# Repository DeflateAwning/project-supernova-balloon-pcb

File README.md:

# Project Supernova
A Helium Balloon, to assess the Helium Network.

## Features
This project is a PCB which is capable of being the primary payload on a PCB aboard a stratospheric helium balloon. The PCB intends to downlink 

* Onboard GPS for position tracking
* Atmospheric condition sensors (temperature/pressure/humidity) to generate downlink data
* Onboard PID-controlled heater and battery management
* Very low cost (<$100)

## Notes
* 3v3 regulated voltage. 9v unregulated battery voltage.
 
## Rev 2 Errata
1. Nothing yet (fingers crossed)

## Rev 1 Errata
1. DHT22 doesn't support 3V3 supply, technically
2. ADC2 doesn't work when wifi is enabled
3. DHT22 cannot be connected to pin D12, as D12 must be floating at boot
4. D34-D39 are input-only (so `TEMP_V+` is a problem)
5. LM335 onboard temperature sensor is basically incompatible with 3V3 systems
6. DHT22 needs a 10k pull-up to 3V3
7. RTF switch needs resistors on each leg to prevent shorting in case of a make-before-break switch.
8. The voltage regulator footprint could use the pads moved a bit (and could include through-hole pins).
9. Should've added a pull-down resistor to the heater MOSFET to prevent heating during boot.
10. Shouldn't have put a via in the pad on the MOSFET, as it prevented the gate from soldering right, then burned the MOSFET when it entered the linear region. Should've used way larger pads on the hand-soldered SOT-23 MOSFET.

### Changes made to correct errata items (Rev 1.1)
* DHT22 (`DHT_DATA`) now connected to D23 (per Errata #3).
* DHT22 now has a 10k pull-up to 3V3 (Errata #6).
* `TEMP_V+` now connected to D25 (per Errata #4), and still left connected to D35.
* LM335 onboard temperature sensor is unused.

### OFIs
* Add LED on HEATER_EN net
* Add LED polarity on silk screen
* Consider 10u cap from GND to EN for programming
* D2 is the onboard LED, so probably best to not use it
* Should have referenced this doc: https://randomnerdtutorials.com/esp32-pinout-reference-gpios/
* Add jumper to disconnect power from GPS (because it uses so much power)

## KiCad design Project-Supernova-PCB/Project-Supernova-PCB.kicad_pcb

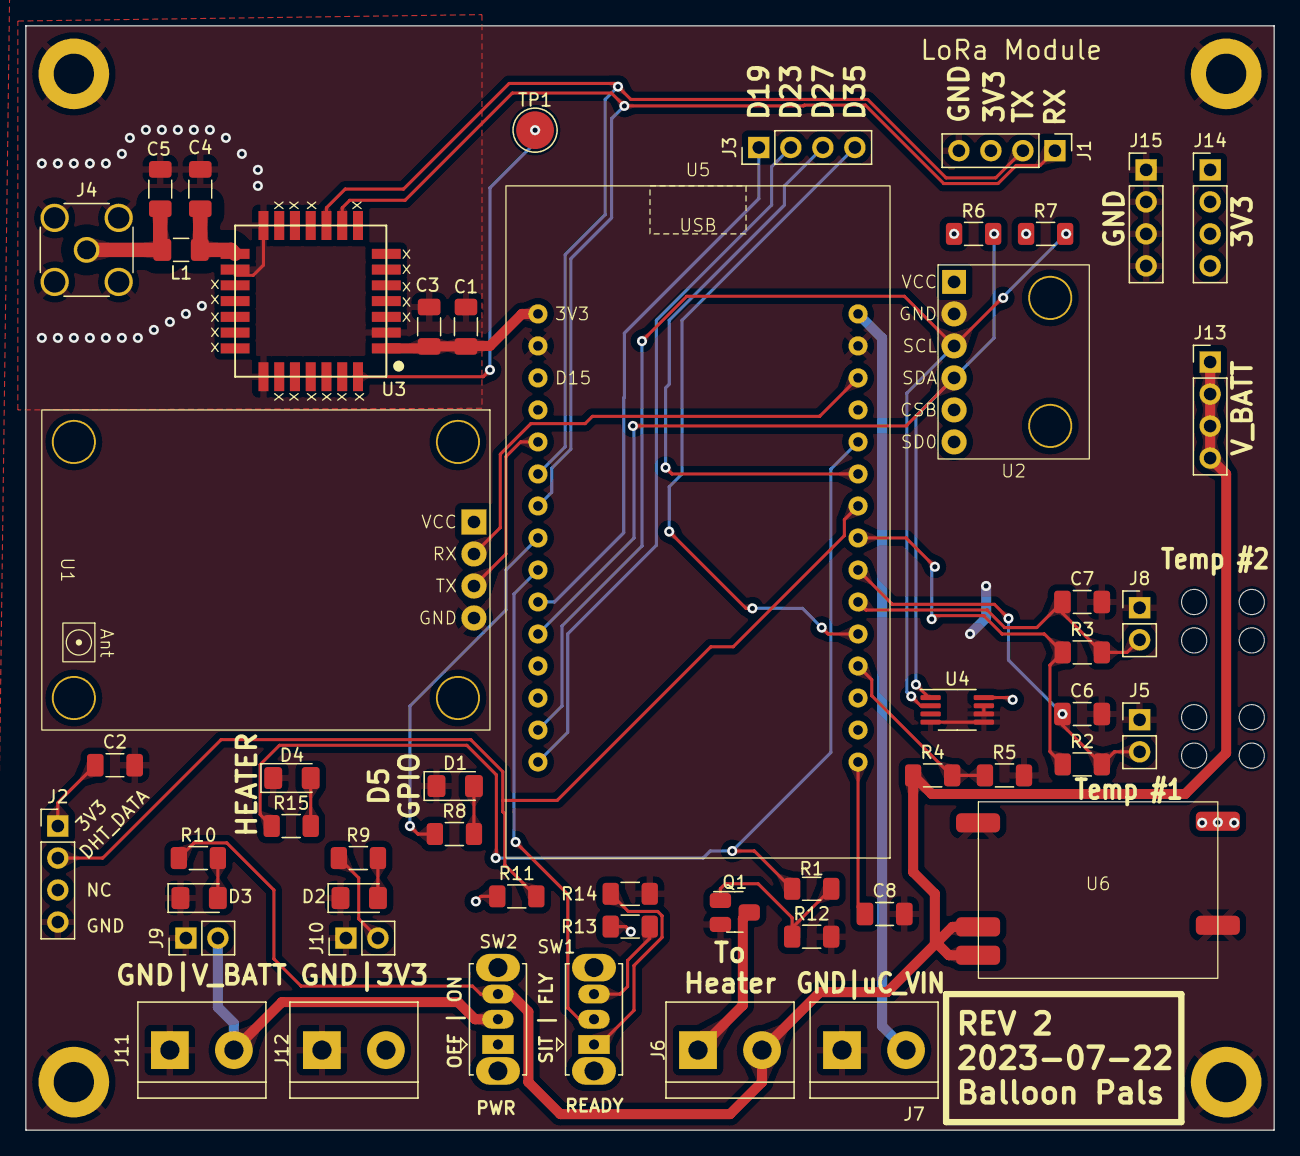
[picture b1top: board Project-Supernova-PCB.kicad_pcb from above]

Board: 2 copper layers, 99.1 x 87.6 mm, 65 parts (0 on the bottom side), 35 nets.

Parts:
C1: 100u; C_1206_3216Metric_Pad1.33x1.80mm_HandSolder
C2: 100n; C_1206_3216Metric_Pad1.33x1.80mm_HandSolder
C3: 4.7u; C_1206_3216Metric_Pad1.33x1.80mm_HandSolder
C4, C5: NC; C_1206_3216Metric_Pad1.33x1.80mm_HandSolder
C6, C7, C8: 10u; C_1206_3216Metric_Pad1.33x1.80mm_HandSolder
D1, D2, D3, D4: LED; LED_1206_3216Metric_Pad1.42x1.75mm_HandSolder
H1, H2, H3, H4: MountingHole_Pad; MountingHole_3.2mm_M3_DIN965_Pad
H5, H6, H7, H8, H9, H10, H11, H12: MountingHole; MountingHole_2mm
J1, J2, J3, J13, J14, J15: Conn_01x04; PinHeader_1x04_P2.54mm_Vertical
J4: Conn_Coaxial; SMA_Wurth_60312002114503_Vertical
J5, J8: 100k_Thermistor; PinHeader_1x02_P2.54mm_Vertical
J6, J7, J11, J12: Screw_Terminal_01x02; TerminalBlock_bornier-2_P5.08mm
J9, J10: Conn_01x02; PinHeader_1x02_P2.54mm_Vertical
L1: 0; L_1206_3216Metric_Pad1.42x1.75mm_HandSolder
Q1: AO3420; SOT-23-MassivePads-HandSolder
R1: 0; R_1206_3216Metric_Pad1.30x1.75mm_HandSolder
R2, R3: 75k; R_1206_3216Metric_Pad1.30x1.75mm_HandSolder
R4: 18k; R_1206_3216Metric_Pad1.30x1.75mm_HandSolder
R5, R6, R7, R13, R14: 4.7k; R_1206_3216Metric_Pad1.30x1.75mm_HandSolder
R8, R9, R15: 1k; R_1206_3216Metric_Pad1.30x1.75mm_HandSolder
R10, R12: 3.3k; R_1206_3216Metric_Pad1.30x1.75mm_HandSolder
R11: 10k; R_1206_3216Metric_Pad1.30x1.75mm_HandSolder
SW1, SW2: SW_SPDT; SW_Slide_1P2T_CK_OS102011MS2Q
TP1: TestPoint; TestPoint_Pad_D3.0mm
U1: GY-NEO6MV2-Module
U2: BMP280-Module
U3: LoRa-E5; LoRa-E5_HandSolder
U4: STDS75DS2F; MSOP-8_3x3mm_P0.65mm
U5: ESP32-Module-30Pin
U6: S09

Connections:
+3V3: C1.1, C2.1, C3.1, J1.3, J2.1, J10.2, J12.2, J14.1, J14.2, J14.3, J14.4, R6.1, R7.1, R9.1, R11.1, R13.1, U1.1 (VCC), U2.1 (VCC), U3.1 (VCC), U4.8 (VDD), U5.1 (3V3), U6.4 (VOUT+)
+BATT: J6.2, J13.1, J13.2, J13.3, J13.4, R4.1, R10.1, SW2.3 (C), U6.2 (VIN+), U6.3 (EN)
BATT_SENSE: R4.2, R5.1, U5.19 (D34/ADC1_CH6)
DHT_DATA: J2.2, R11.2, U5.24 (D26/ADC2_CH9/DAC2)
GND: C1.2, C2.2, C3.2, C4.2, C5.2, C6.2, C7.2, C8.2, D1.1 (K), D2.1 (K), D3.1 (K), D4.1 (K), H1.1, H2.1, H3.1, H4.1, J1.4, J2.4, J4.2 (Ext), J5.1, J7.1, J8.1, J9.1, J10.1, J11.1, J12.1, J15.1, J15.2, J15.3, J15.4, Q1.2 (S), R5.2, R12.2, R14.2, U1.4 (GND), U2.2 (GND), U3.2 (GND), U3.14 (GND), U3.16 (GND), U3.22 (GND), U4.4 (GND), U4.5 (A2), U4.6 (A1), U4.7 (A0), U5.2 (GND_2), U5.29 (GND_1), U6.1 (VIN-), U6.5 (VOUT-)
GPS_UART_MISO: U1.3 (TX), U5.5 (D4/ADC2_CH0/TOUCH0)
GPS_UART_MOSI: U1.2 (RX), U5.28 (D13/ADC2_CH4/TOUCH4/HSPI_MOSI)
HEATER_EN: R1.1, R15.1, U5.26 (D14/ADC2_CH6/TOUCH6/HSPI_CLK)
LORA_UART_MISO: J1.2, U3.10 (PB6), U5.6 (RX2/D16)
LORA_UART_MOSI: J1.1, U3.9 (PB7), U5.7 (TX2/D17)
MCU_VIN: J7.2, U5.30 (VIN)
unnamed: D1.2 (A), R8.2
unnamed: D2.2 (A), R9.2
unnamed: D3.2 (A), R10.2
unnamed: D4.2 (A), R15.2
unnamed: J3.1, U5.10 (D19/VSPI_MISO)
unnamed: J3.2, U5.15 (D23/VSPI_MOSI)
unnamed: J3.3, U5.25 (D27/ADC2_CH7/TOUCH7)
unnamed: J3.4, U5.20 (D35/ADC1_CH7)
unnamed: C5.1, J4.1 (In), L1.2
unnamed: J6.1, Q1.3 (D)
unnamed: J9.2, J11.2, SW2.2 (B)
unnamed: Q1.1 (G), R1.2, R12.1
unnamed: R14.1, SW1.1 (A)
unnamed: R13.2, SW1.3 (C)
unnamed: TP1.1, U3.28 (PB0)
unnamed: C4.1, L1.1, U3.15 (RFIO)
unnamed: R8.1, U5.8 (D5/VSPI_CS0)
unnamed: C8.1, U5.16 (EN)
RTF_SWITCH: SW1.2 (B), U5.9 (D18/VSPI_CLK)
SCL: R7.2, U2.3 (SCL), U4.2 (SCL), U5.14 (D22/I2C_SCL)
SDA: R6.2, U2.4 (SDA), U4.1 (SDA), U5.11 (D21/I2C_SDA)
TEMP_SENSE_1: C6.1, J5.2, R2.2, U5.22 (D33/ADC1_CH5/TOUCH8)
TEMP_SENSE_2: C7.1, J8.2, R3.2, U5.21 (D32/ADC1_CH4/TOUCH9)
TEMP_V+: R2.1, R3.1, U5.23 (D25/ADC2_CH8/DAC1)

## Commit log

2023-03-18 Add basic README
2023-04-09 Add GPS and BMP280 symbols and footprints
2023-04-10 Add more parts of schematic
2023-04-10 Update schematic docs, add TODO
2023-04-24 Add S09 symbol and footprint
2023-04-26 Add ESP32 microcontroller
2023-04-26 Add better LoRa footprint and better ESP symbol
2023-04-29 More work
2023-05-18 Plot latest schematic
2023-05-20 Connected MCU pins
2023-05-20 Lay out PCB
2023-05-20 Routed PCB
2023-05-20 Gerbers and such
2023-05-21 PCB changes, finish Rev1 as ordered
2023-07-19 Add Rev1.1 hot fix notes
2023-07-19 Main Rev2 schematic changes
2023-07-23 Lock in Rev2 Gerber
2023-07-24 Fix DRC, republish V2
2023-07-24 Add teardrops in Gerber
2023-12-25 Clean up very messy schematic
2023-12-31 Update schematic page size
